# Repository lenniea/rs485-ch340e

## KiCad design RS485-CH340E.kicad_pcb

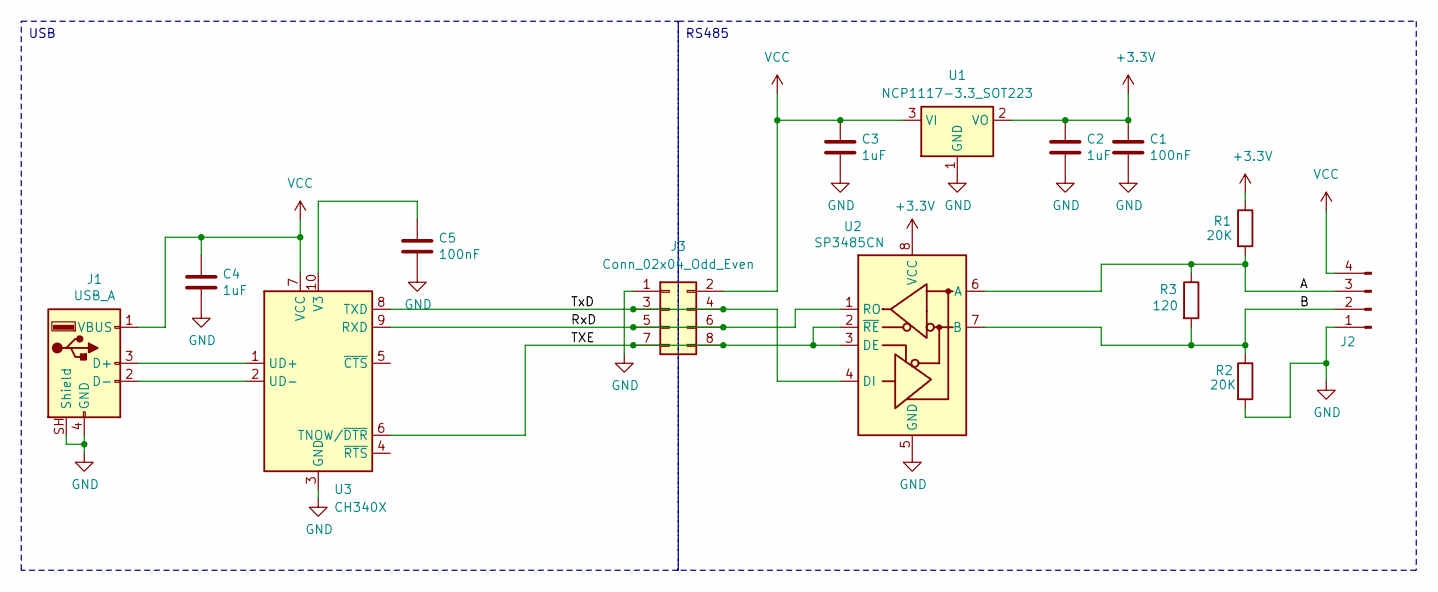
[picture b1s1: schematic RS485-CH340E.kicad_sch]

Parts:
C1, C5: 100nF; C_0603_1608Metric
C2, C3, C4: 1uF; C_0603_1608Metric
J1: USB_A; USB_A_CNCTech_1001-011-01101_Horizontal
J2: Conn_01x04_Pin; PinHeader_1x04_P2.54mm_Horizontal
J3: Conn_02x04_Odd_Even; PinHeader_2x04_P1.27mm_Vertical
R1, R2: 20K; R_0603_1608Metric
R3: 120; R_0603_1608Metric
U1: NCP1117-3.3_SOT223; SOT-23
U2: SP3485CN; SOIC-8_3.9x4.9mm_P1.27mm
U3: CH340X; MSOP-10_3x3mm_P0.5mm

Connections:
+3.3V: C1.1, C2.1, R1.1, U1.2 (VO), U2.8 (VCC)
/A: J2.3, R1.2, R3.1, U2.6 (A)
/B: J2.2, R2.1, R3.2, U2.7 (B)
/RxD: J3.5, J3.6, U2.1 (RO), U3.9 (RXD)
/TXE: J3.7, J3.8, U2.2 (~RE), U2.3 (DE), U3.6 (TNOW/~DTR)
/TxD: J3.3, J3.4, U2.4 (DI), U3.8 (TXD)
GND: C1.2, C2.2, C3.2, C4.2, C5.2, J1.4 (GND), J1.SH (Shield), J2.1, J3.1, R2.2, U1.1 (GND), U2.5 (GND), U3.3 (GND)
unnamed: J1.3 (D+), U3.1 (UD+)
unnamed: J1.2 (D-), U3.2 (UD-)
unnamed: C5.1, U3.10 (V3)
VCC: C3.1, C4.1, J1.1 (VBUS), J2.4, J3.2, U1.3 (VI), U3.7 (VCC)

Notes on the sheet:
USB
RS485

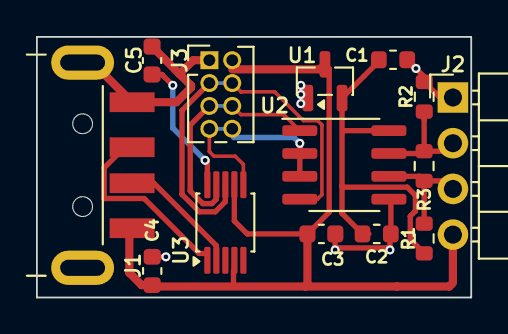
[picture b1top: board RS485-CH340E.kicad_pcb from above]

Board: 2 copper layers, 24.1 x 14.5 mm, 14 parts (0 on the bottom side), 11 nets.
